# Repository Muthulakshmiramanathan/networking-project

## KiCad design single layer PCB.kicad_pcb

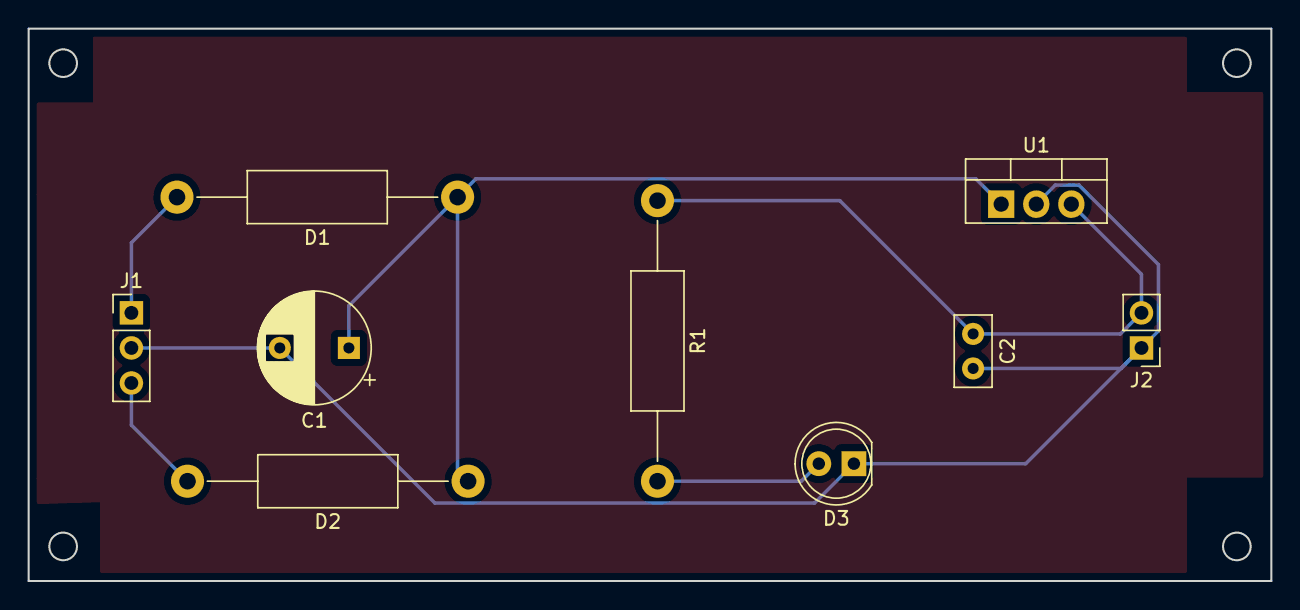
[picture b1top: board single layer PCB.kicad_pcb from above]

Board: 2 copper layers, 90.0 x 40.0 mm, 9 parts (0 on the bottom side), 6 nets.

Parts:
C1: 1000uF; CP_Radial_D8.0mm_P5.00mm
C2: 0.1uF; C_Disc_D5.0mm_W2.5mm_P2.50mm
D1: 1N4007; R_Axial_DIN0411_L9.9mm_D3.6mm_P20.32mm_Horizontal
D2: 1n4007; R_Axial_DIN0411_L9.9mm_D3.6mm_P20.32mm_Horizontal
D3: LED; LED_D5.0mm
J1: Conn_01x03_Male; PinHeader_1x03_P2.54mm_Vertical
J2: Conn_01x02_Male; PinHeader_1x02_P2.54mm_Vertical
R1: 150; R_Axial_DIN0411_L9.9mm_D3.6mm_P20.32mm_Horizontal
U1: L7805; TO-220-3_Vertical

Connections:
+Vac: D1.2, J1.1
+Vo: C2.1, J2.2, R1.1, U1.3
-Vac: D2.2, J1.3
GND: C1.2, C2.2, D3.1, J1.2, J2.1, U1.2
unnamed: C1.1, D1.1, D2.1, U1.1
unnamed: D3.2, R1.2

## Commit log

2026-04-13 Initial commit - TCP, UDP, MQTT projects
2026-04-13 Added UDP and TCP client/server files
